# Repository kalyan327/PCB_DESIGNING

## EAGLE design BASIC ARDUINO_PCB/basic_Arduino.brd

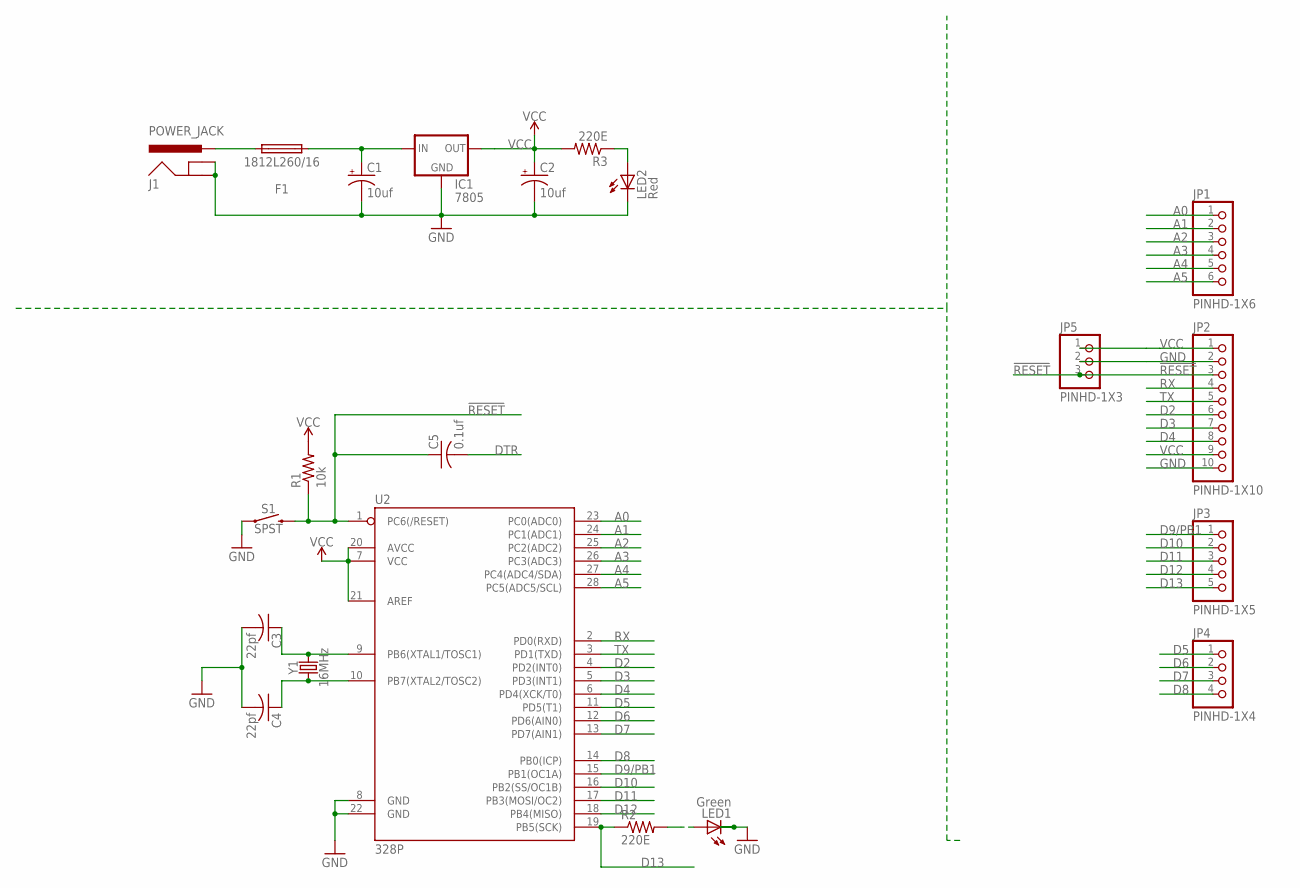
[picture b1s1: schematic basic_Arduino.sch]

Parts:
C1, C2: 10uf; E2,5-6E
C3, C4: 22pf; C025-024X044
C5: 0.1uf; C025-024X044
F1: 1812L260/16; FUSC4532X125
IC1: 7805; 78XXS
J1: POWER_JACK; POWER_JACK_PTH
JP1: PINHD-1X6; 1X06
JP2: PINHD-1X10; 1X10
JP3: PINHD-1X5; 1X05
JP4: PINHD-1X4; 1X04
JP5: PINHD-1X3; 1X03
LED1: Green; LED3MM
LED2: Red; LED3MM
R1: 10k; 0204/7
R2, R3: 220E; 0204/7
S1: SPST; TACTILE_SWITCH_PTH_6.0MM
U2: 328P; DIP28
Y1: 16MHz; HC49US

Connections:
!RESET: C5.1, JP2.3, JP5.3, R1.1, S1.3 (2), U2.1 (PC6(/RESET))
A0: JP1.1, U2.23 (PC0(ADC0))
A1: JP1.2, U2.24 (PC1(ADC1))
A2: JP1.3, U2.25 (PC2(ADC2))
A3: JP1.4, U2.26 (PC3(ADC3))
A4: JP1.5, U2.27 (PC4(ADC4/SDA))
A5: JP1.6, U2.28 (PC5(ADC5/SCL))
D2: JP2.6, U2.4 (PD2(INT0))
D3: JP2.7, U2.5 (PD3(INT1))
D4: JP2.8, U2.6 (PD4(XCK/T0))
D5: JP4.1, U2.11 (PD5(T1))
D6: JP4.2, U2.12 (PD6(AIN0))
D7: JP4.3, U2.13 (PD7(AIN1))
D8: JP4.4, U2.14 (PB0(ICP))
D9/PB1: JP3.1, U2.15 (PB1(OC1A))
D10: JP3.2, U2.16 (PB2(SS/OC1B))
D11: JP3.3, U2.17 (PB3(MOSI/OC2))
D12: JP3.4, U2.18 (PB4(MISO))
D13: JP3.5, R2.1, U2.19 (PB5(SCK))
DTR: C5.2
GND: C1.-, C2.-, C3.2, C4.2, IC1.GND, J1.GND, J1.GNDBREAK, JP2.2, JP2.10, JP5.2, LED1.K (C), LED2.K (C), S1.1, U2.8 (GND), U2.22 (GND)
unnamed: C1.+, F1.2, IC1.IN
unnamed: C3.1, U2.9 (PB6(XTAL1/TOSC1)), Y1.2
unnamed: C4.1, U2.10 (PB7(XTAL2/TOSC2)), Y1.1
unnamed: LED1.A, R2.2
unnamed: LED2.A, R3.1
unnamed: F1.1, J1.PWR
RX: JP2.4, U2.2 (PD0(RXD))
TX: JP2.5, U2.3 (PD1(TXD))
VCC: C2.+, IC1.OUT, JP2.1, JP2.9, JP5.1, R1.2, R3.2, U2.7 (VCC), U2.20 (AVCC), U2.21 (AREF)

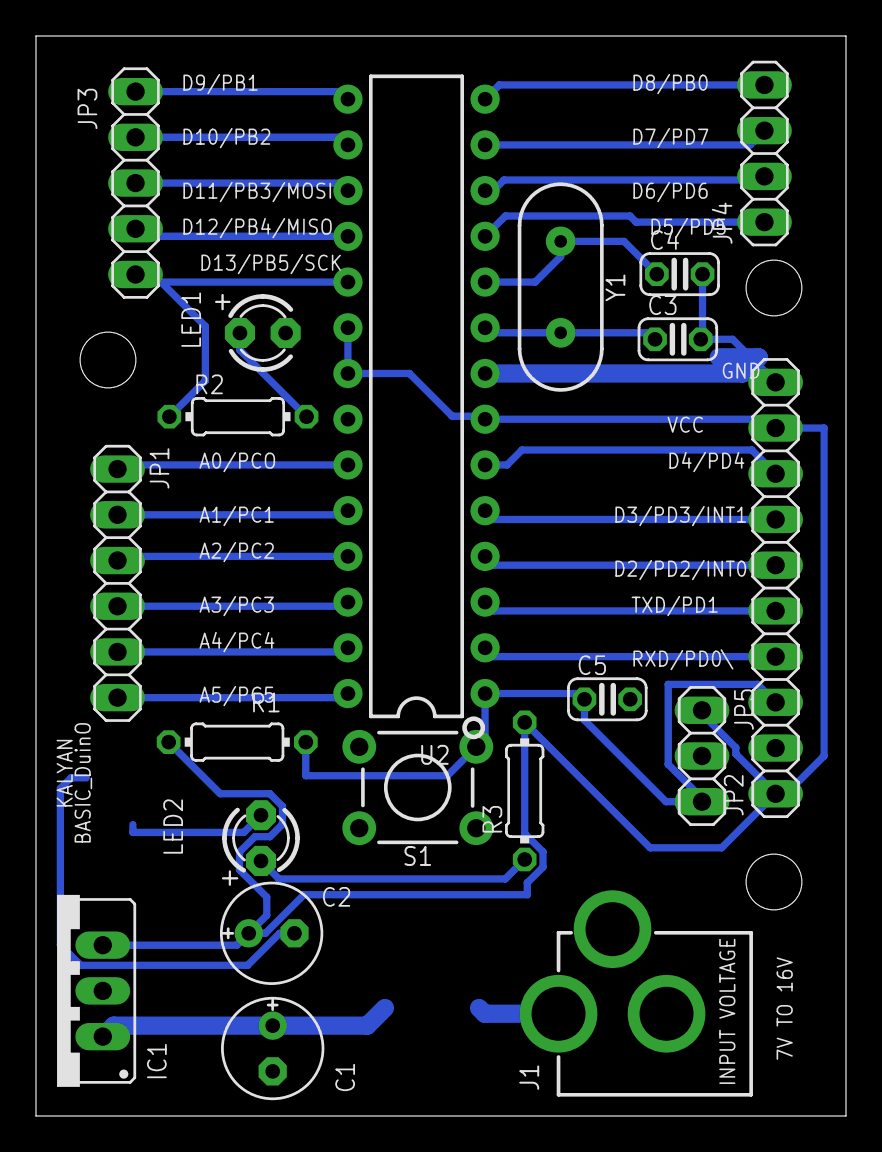
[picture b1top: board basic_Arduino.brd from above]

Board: 2 copper layers, 45.0 x 60.0 mm, 21 parts (1 on the bottom side), 29 nets.

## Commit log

2023-08-09 Add files via upload
    Here are the files for voltage regulator of 5v
2023-08-09 Add files via upload
    Here are the board schematic and PCB design for basic Arduino.
2023-08-11 Add files via upload
    These are the Gerber files for LED SEQUENCER.
2023-08-11 Add files via upload
    GERBER FILES FOR 5V_VOLTAGE REGULATOR
2023-08-12 Add files via upload
    Here are the schematic and PCB files for H-bridge circuit, which is motor controlling board.
2023-08-15 Add files via upload
    Here are the schematic, pcb board and gerber files for node mcu project.
2023-08-18 Add files via upload
    These are the Gerber files for led-chaser PCB
2023-08-18 These are the PCB files for gas sensor
2023-08-22 Add files via upload
    These are the Gerber files for Multipurpose PCB

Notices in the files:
parts and their libraries:
SparkFun-Connectors: Licensing: Creative Commons ShareAlike 4.0 International - https://creativecommons.org/licenses/by-sa/4.0
